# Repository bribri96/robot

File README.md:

# Repo che contiene il mio progetto di maturità

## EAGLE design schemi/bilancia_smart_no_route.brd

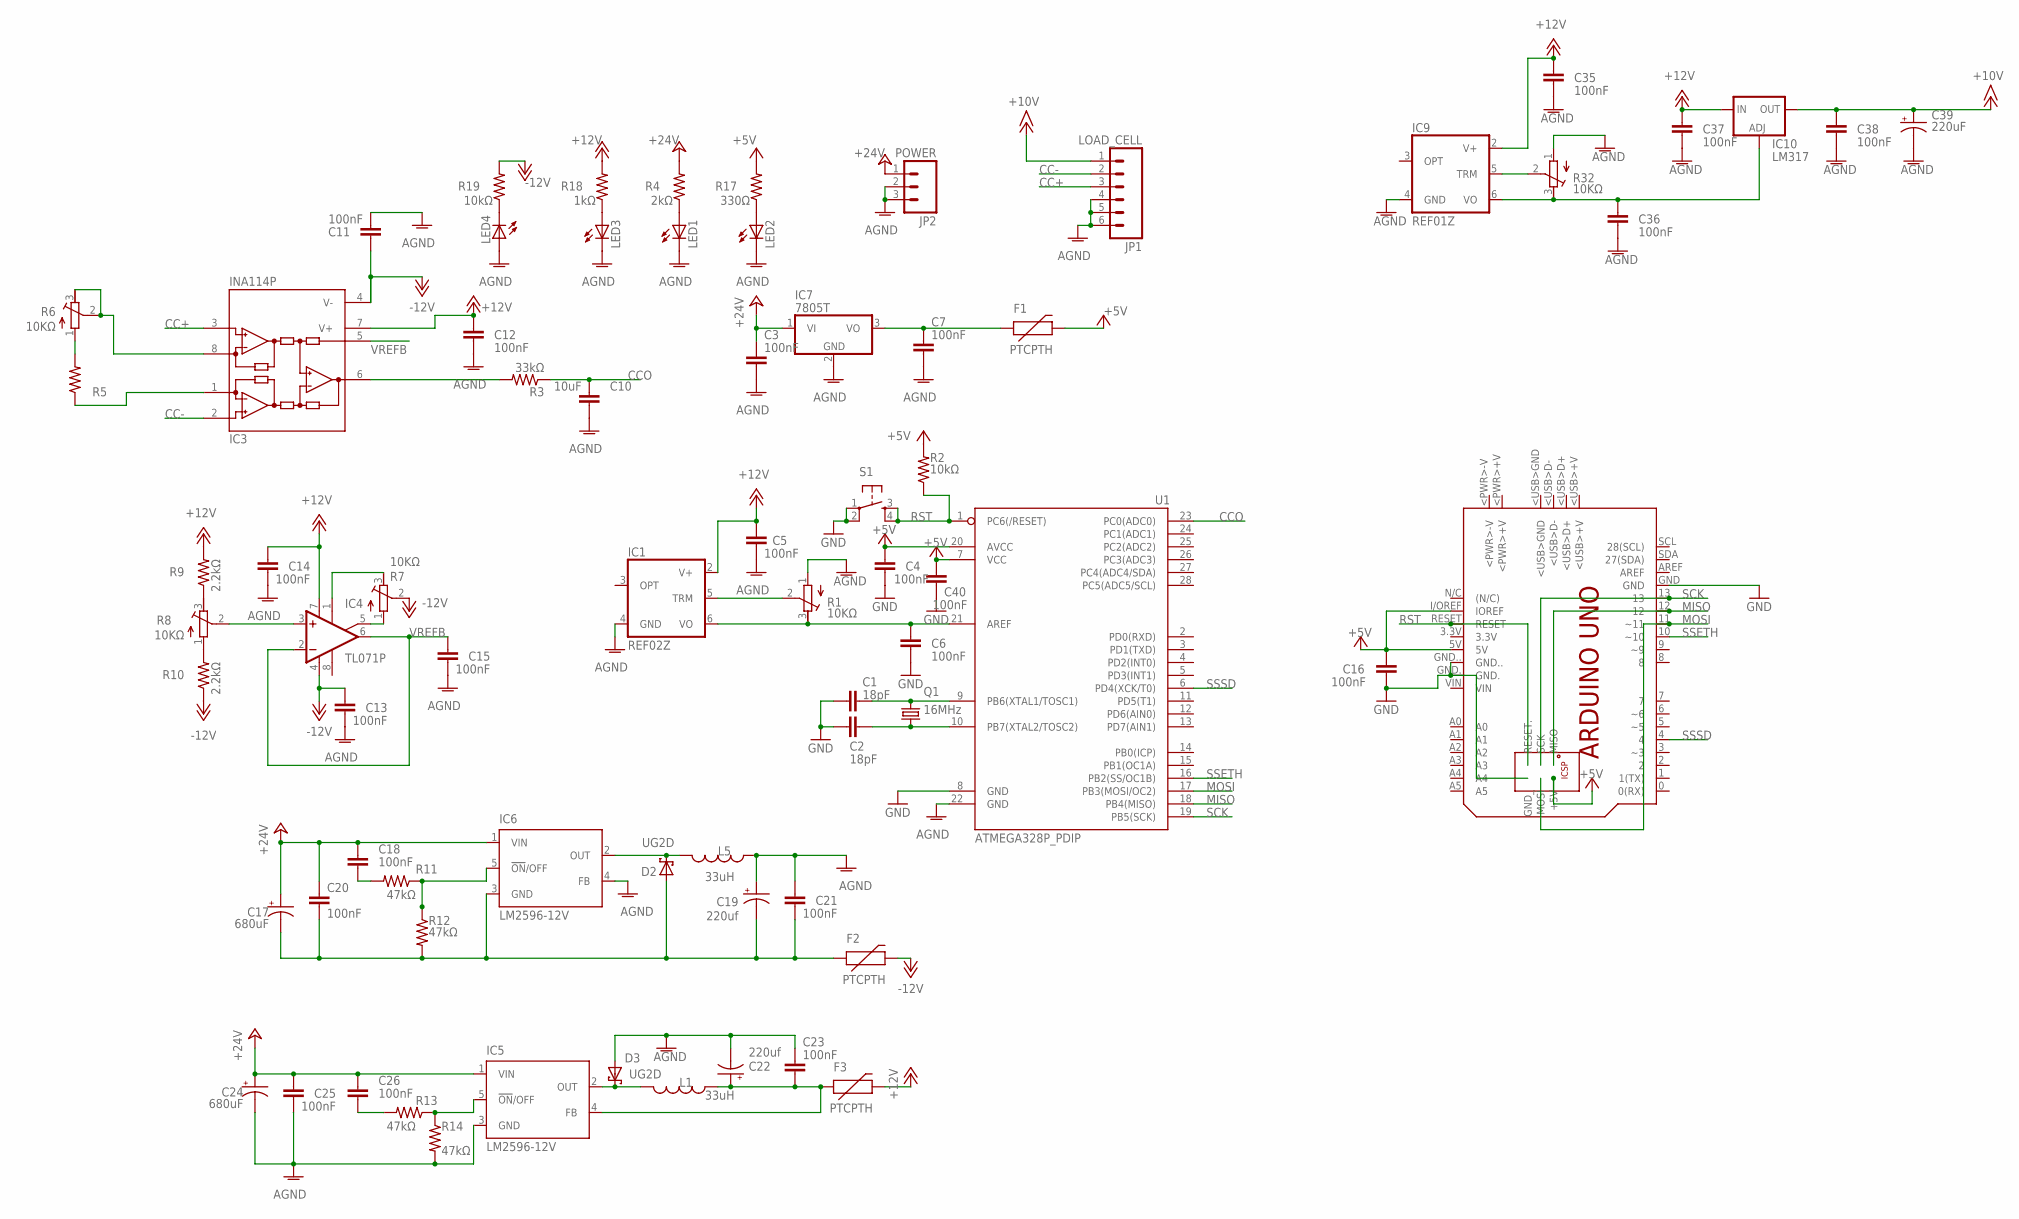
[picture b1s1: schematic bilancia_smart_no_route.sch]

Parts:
C1, C2: 18pF; C2.5-2
C3, C4, C5, C6, C7, C11, C12, C13, C14, C15, C16, C18, C20, C21, C23, C25, C26, C35, C36, C37, C38, C40: 100nF; C2.5-2
C10: 10uF; C2.5-2
C17, C24: 680uF; E5-8,5
C19, C22: 220uf; E5-8,5
C39: 220uF; CPOL-RADIAL-100UF-25V
D2, D3: UG2D; DO41-7
F1, F2, F3: PTCPTH; PTC
IC1: REF02Z; DIL08
IC3: INA114P; DIL08
IC4: TL071P; DIL08
IC5, IC6: LM2596-12V; T05D
IC7: 7805T; TO220H
IC9: REF01Z; DIL08
IC10: LM317; 317TS
JP1: LOAD_CELL; 1X06
JP2: POWER; 1X03
L1, L5: 33uH; RLB0912
LED1, LED2, LED3, LED4: MINIMIDI_LED5MM
PCB1: ARDUINO_UNO
Q1: 16MHz; HC49/S
R1, R6, R7, R8, R32: 10KΩ; RTRIM64W
R2, R19: 10kΩ; 0207/10
R3: 33kΩ; 0207/10
R4: 2kΩ; 0207/10
R5: R-US_0207/10; 0207/10
R9, R10: 2.2kΩ; 0207/10
R11, R12, R13, R14: 47kΩ; 0207/2V
R17: 330Ω; 0207/10
R18: 1kΩ; 0207/10
S1: TAC_SWITCHPTH; TACTILE-PTH
U1: ATMEGA328P_PDIP; DIL28-3

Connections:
+5V: C4.2, C16.2, C40.2, F1.P$2 (2), PCB1.5V, PCB1.+5V, PCB1.I/OREF (IOREF), R2.2, R17.2, U1.7 (VCC), U1.20 (AVCC)
+12V: C5.1, C12.2, C14.2, C35.2, C37.2, F3.P$2 (2), IC1.2 (V+), IC3.7 (V+), IC4.7 (V+), IC9.2 (V+), IC10.3 (IN), R9.2, R18.2
+15V: C38.2, C39.1 (+), IC10.2 (OUT), JP1.1
+24V: C3.2, C17.+, C18.1, C20.1, C24.+, C25.1, C26.1, IC5.1 (VIN), IC6.1 (VIN), IC7.1 (VI), JP2.1, R4.2
-12V: C11.2, C13.2, F2.P$2 (2), IC3.4 (V-), IC4.4 (V-), R7.2 (S), R10.1, R19.2
AGND: C3.1, C5.2, C7.1, C10.1, C11.1, C12.1, C13.1, C14.1, C15.1, C19.+, C21.1, C22.-, C23.2, C24.-, C25.2, C35.1, C36.1, C37.1, C38.1, C39.2 (-), D3.A, IC1.4 (GND), IC5.3 (GND), IC6.4 (FB), IC7.2 (GND), IC9.4 (GND), JP1.4, JP1.5, JP1.6, JP2.2, JP2.3, L5.1, LED1.K (C), LED2.K (C), LED3.K (C), LED4.A, R1.1 (E), R14.2, R32.1 (E), U1.22 (GND)
CC+: IC3.3 (+IN), JP1.3
CC-: IC3.2 (-IN), JP1.2
CCO: C10.2, R3.1, U1.23 (PC0(ADC0))
GND: C1.1, C2.1, C4.1, C6.1, C16.1, C40.1, PCB1.GND, PCB1.GND., PCB1.GND.., PCB1.GND_, S1.1, S1.2, U1.8 (GND)
MISO: PCB1.12, PCB1.MISO, U1.18 (PB4(MISO))
MOSI: PCB1.11 (~11), PCB1.MOSI, U1.17 (PB3(MOSI/OC2))
unnamed: C6.2, IC1.6 (VO), R1.3 (A), U1.21 (AREF)
unnamed: C2.2, Q1.2, U1.10 (PB7(XTAL2/TOSC2))
unnamed: C1.2, Q1.1, U1.9 (PB6(XTAL1/TOSC1))
unnamed: LED2.A, R17.1
unnamed: IC1.5 (TRM), R1.2 (S)
unnamed: C7.2, F1.P$1 (1), IC7.3 (VO)
unnamed: IC3.6 (OUT), R3.2
unnamed: LED1.A, R4.1
unnamed: R5.2, R6.1 (E)
unnamed: IC3.8 (RG), R6.2 (S), R6.3 (A)
unnamed: IC3.1 (RG), R5.1
unnamed: IC4.5 (ON2), R7.1 (E)
unnamed: IC4.1 (ON1), R7.3 (A)
unnamed: IC6.5 (!ON!/OFF), R11.1, R12.1
unnamed: R8.3 (A), R9.1
unnamed: R8.1 (E), R10.2
unnamed: IC4.3 (+IN), R8.2 (S)
unnamed: C18.2, R11.2
unnamed: D2.C, IC6.2 (OUT), L5.2
unnamed: C22.+, C23.1, F3.P$1 (1), IC5.4 (FB), L1.1
unnamed: C17.-, C19.-, C20.2, C21.2, D2.A, F2.P$1 (1), IC6.3 (GND), R12.2
unnamed: D3.C, IC5.2 (OUT), L1.2
unnamed: IC5.5 (!ON!/OFF), R13.1, R14.1
unnamed: C26.2, R13.2
unnamed: LED3.A, R18.1
unnamed: LED4.K (C), R19.1
unnamed: C36.2, IC9.6 (VO), IC10.1 (ADJ), R32.3 (A)
unnamed: IC9.5 (TRM), R32.2 (S)
RST: PCB1.RESET, PCB1.RESET., R2.1, S1.3, S1.4, U1.1 (PC6(/RESET))
SCK: PCB1.13, PCB1.SCK, U1.19 (PB5(SCK))
SSETH: PCB1.10 (~10), U1.16 (PB2(SS/OC1B))
SSSD: PCB1.4, U1.6 (PD4(XCK/T0))
VREFB: C15.2, IC3.5 (REF), IC4.2 (-IN), IC4.6 (OUT)

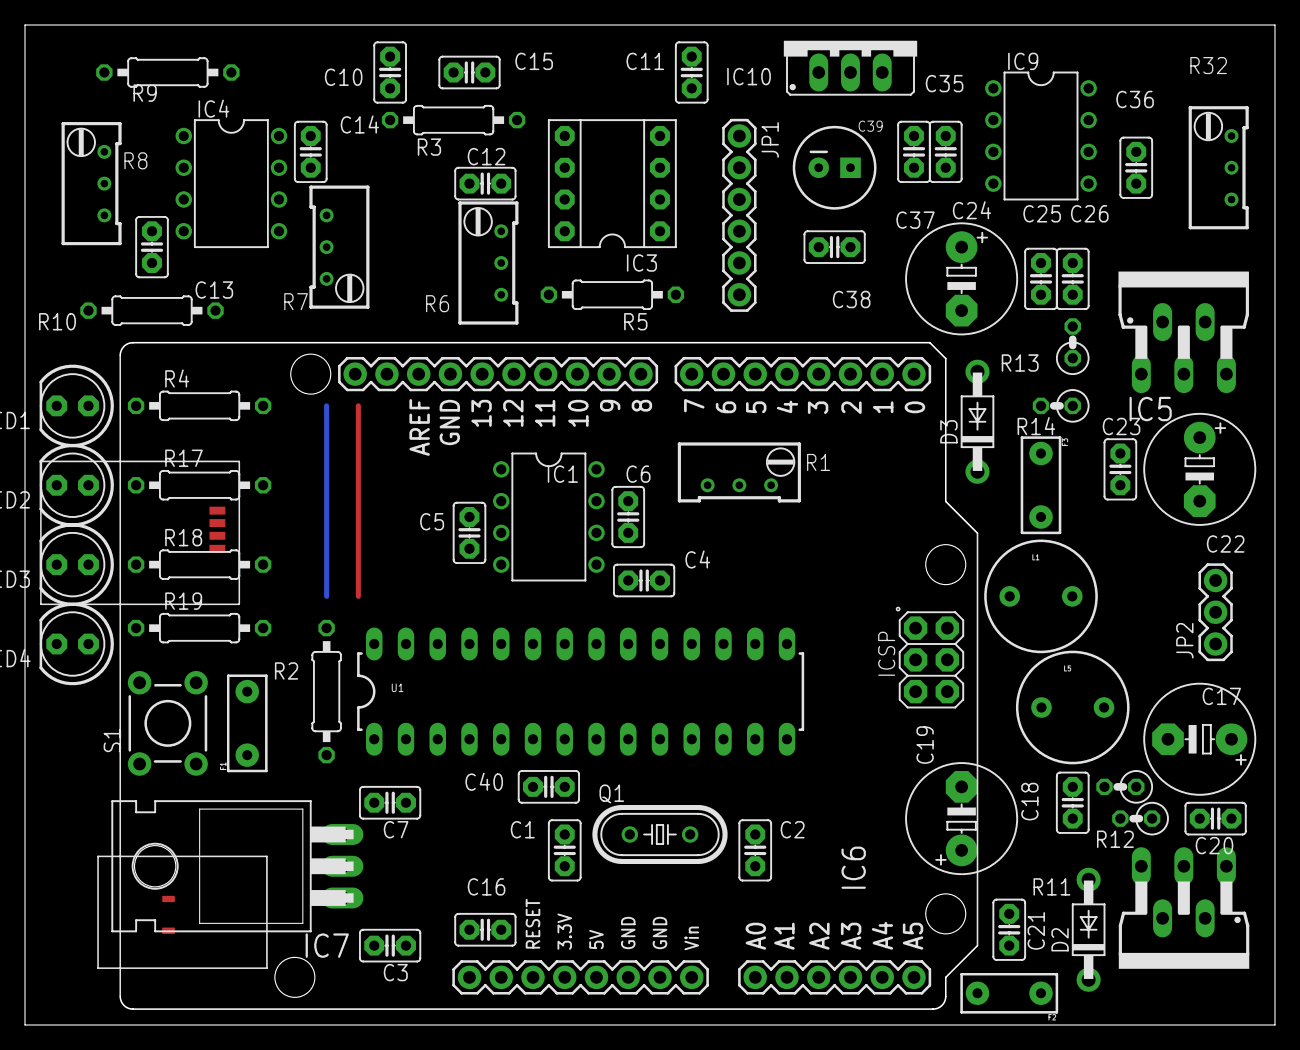
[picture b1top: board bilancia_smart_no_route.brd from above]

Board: 2 copper layers, 100.0 x 80.0 mm, 73 parts (0 on the bottom side), 45 nets.

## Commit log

2015-07-31 test
2015-07-31 tesina

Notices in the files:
parts and their libraries:
SparkFun-PowerIC: Licensing: CC v3.0 Share-Alike You are welcome to use this library for commercial purposes.
